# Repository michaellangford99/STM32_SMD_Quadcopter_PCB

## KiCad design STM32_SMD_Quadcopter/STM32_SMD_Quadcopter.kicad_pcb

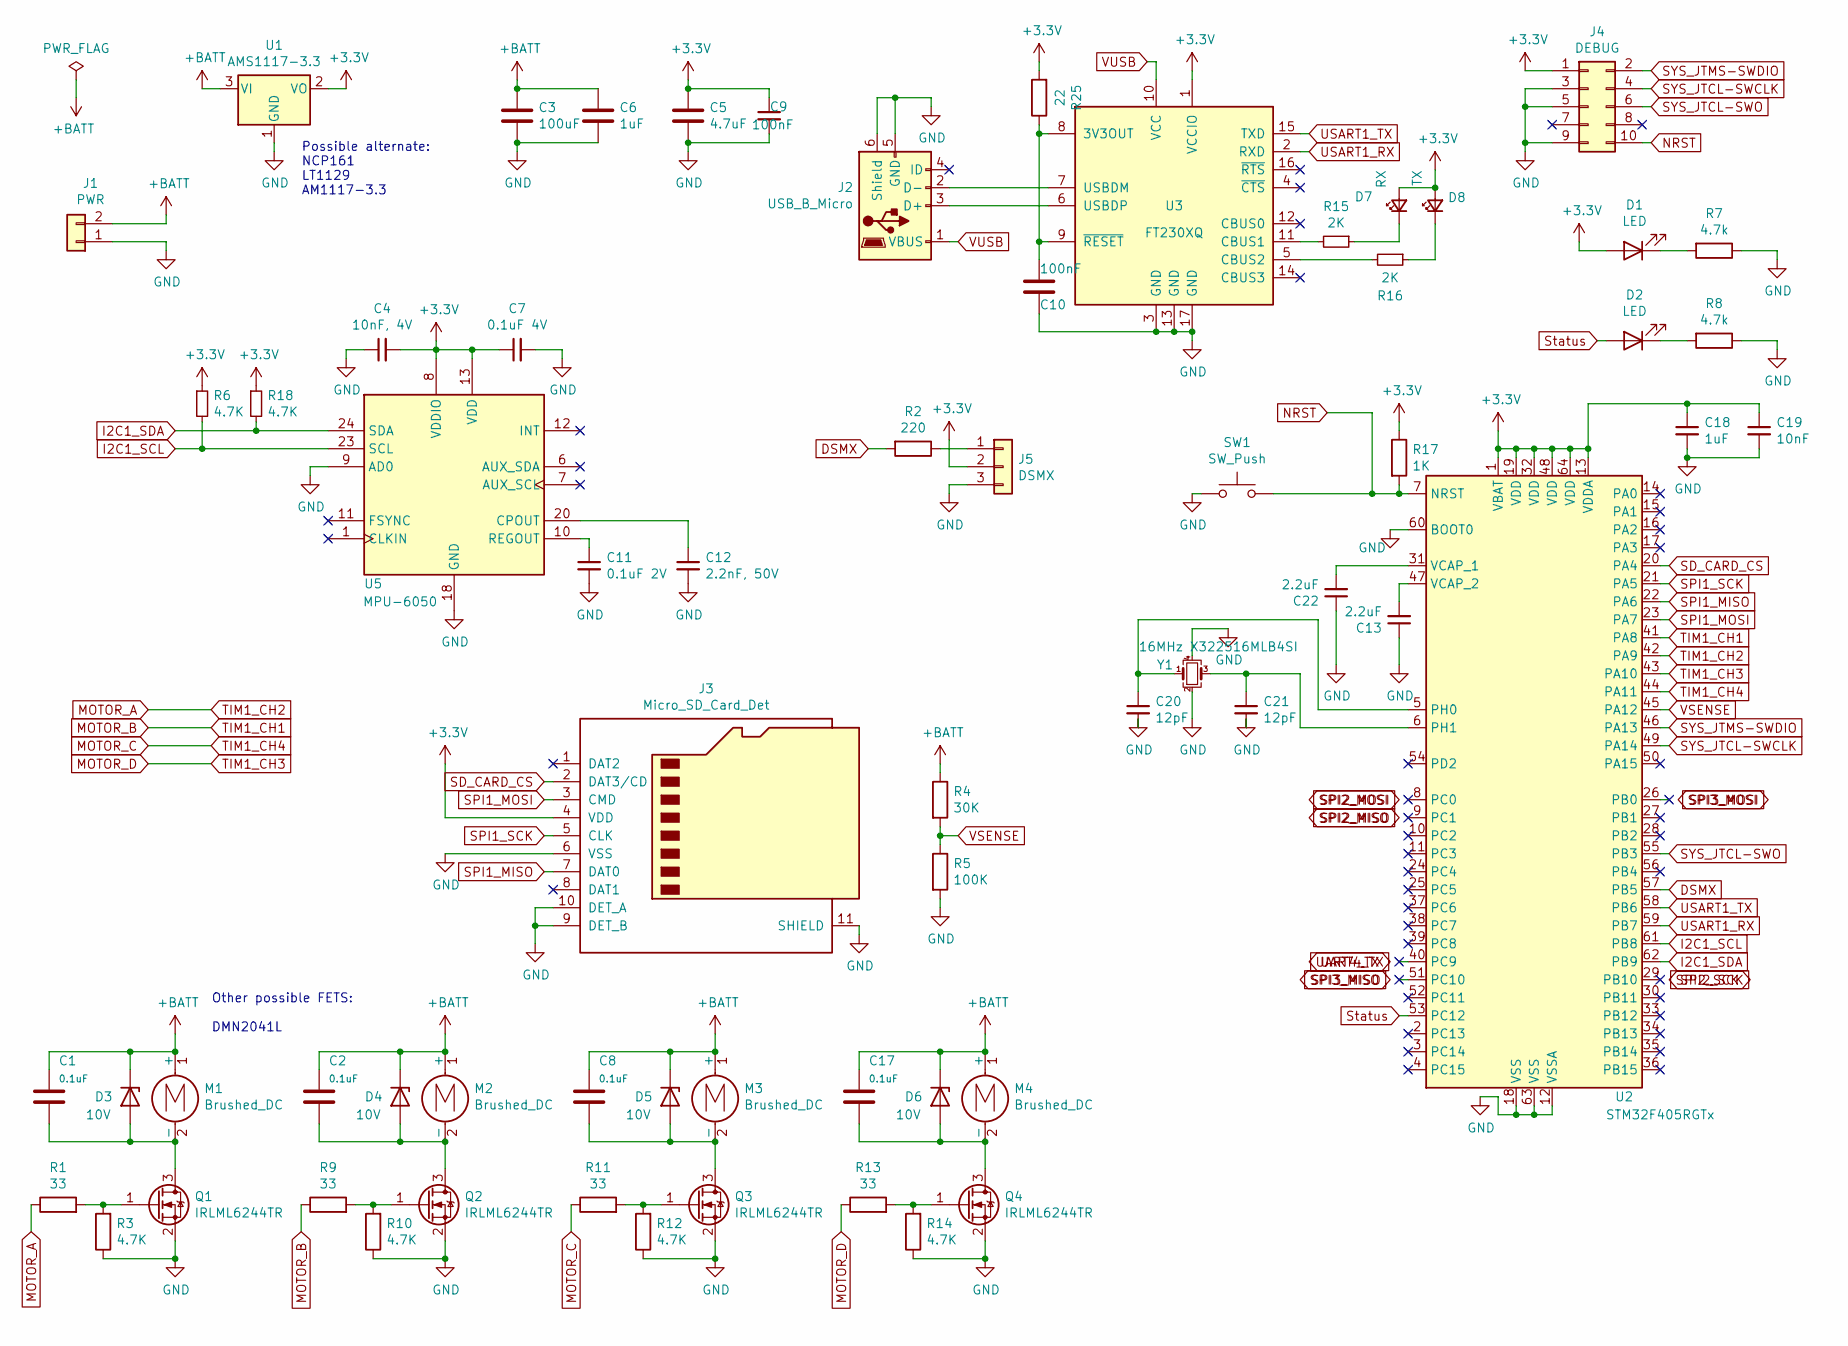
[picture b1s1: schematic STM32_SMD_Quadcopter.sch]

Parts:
C1, C2, C8, C17: 0.1uF; C_0402_1005Metric; LCSC Part # C1525
C3: 100uF; C_Elec_3x5.4; JLCPCB BOM 0
C4: 10nF, 4V; C_0402_1005Metric; LCSC Part # C15195
C5: 4.7uF; C_1210_3225Metric; JLCPCB BOM 0
C6, C18: 1uF; C_0603_1608Metric; LCSC Part # C15849
C7: 0.1uF 4V; C_0402_1005Metric; LCSC Part # C1525
C9, C10: 100nF; C_0402_1005Metric; LCSC Part # C1525
C11: 0.1uF 2V; C_0402_1005Metric; LCSC Part # C1525
C12: 2.2nF, 50V; C_0805_2012Metric; LCSC Part # C28260
C13, C22: 2.2uF; C_0603_1608Metric; LCSC Part # C23630
C19: 10nF; C_0603_1608Metric; LCSC Part # C57112
C20, C21: 12pF; C_0603_1608Metric; LCSC Part # C38523
D1: LED; LED_0603_1608Metric; LCSC Part # C72038
D2: LED; LED_0603_1608Metric; LCSC Part # C72043
D3, D4, D5, D6: 10V; D_0805_2012Metric; JLCPCB BOM 0
D7: RX; LED_0603_1608Metric; LCSC Part # C72041
D8: TX; LED_0603_1608Metric; LCSC Part # C2286
J1: PWR; PinHeader_1x02_P2.54mm_Vertical; JLCPCB BOM 0
J2: USB_B_Micro; USB_Micro-B_Molex_47346-0001; JLCPCB BOM 0
J3: Micro_SD_Card_Det; microSD_HC_Hirose_DM3D-SF; JLCPCB BOM 0
J4: DEBUG; PinSocket_2x05_P1.27mm_Vertical_SMD; JLCPCB BOM 0
J5: DSMX; PinHeader_1x03_P2.54mm_Vertical; JLCPCB BOM 0
M1, M2, M3, M4: Brushed_DC; PinHeader_1x02_P2.00mm_Vertical; JLCPCB BOM 0
Q1, Q2, Q3, Q4: IRLML6244TR; SOT-23_Handsoldering; JLCPCB BOM 0
R1, R9, R11, R13: 33; R_0603_1608Metric; LCSC Part # C23140
R2: 220; R_0603_1608Metric; LCSC Part # C22962
R3, R6, R10, R12, R14, R18: 4.7K; R_0603_1608Metric; LCSC Part # C23162
R4: 30K; R_0603_1608Metric; LCSC Part # C22984
R5: 100K; R_0603_1608Metric; LCSC Part # C25803
R7, R8: 4.7k; R_0603_1608Metric; LCSC Part # C23162
R15, R16: 2K; R_0603_1608Metric; LCSC Part # C22975
R17: 1K; R_0603_1608Metric; LCSC Part # C21190
R25: 22; R_0402_1005Metric; LCSC Part # C25092
SW1: SW_Push; SW_SPST_B3U-1000P; JLCPCB BOM 0
U1: AMS1117-3.3; SOT-223-3_TabPin2; JLCPCB BOM 0
U2: STM32F405RGTx; LQFP-64_10x10mm_P0.5mm
U3: FT230XQ; QFN-16-1EP_4x4mm_P0.65mm_EP2.5x2.5mm; LCSC Part # C128629
U5: MPU-6050; InvenSense_QFN-24_4x4mm_P0.5mm; LCSC Part # C24112
Y1: 16MHz X322516MLB4SI; Crystal_SMD_3225-4Pin_3.2x2.5mm; LCSC Part # C13738

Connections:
+3V3: C4.2, C5.1, C7.1, C9.1, C18.1, C19.1, D1.2 (A), D7.2 (A), D8.2 (A), J3.4 (VDD), J4.1, J5.2, R6.1, R17.1, R18.1, R25.2, U1.2 (VO), U2.1 (VBAT), U2.13 (VDDA), U2.19 (VDD), U2.32 (VDD), U2.48 (VDD), U2.64 (VDD), U3.1 (VCCIO), U5.8 (VDDIO), U5.13 (VDD); also elsewhere on the board
+BATT: C1.1, C2.1, C3.1, C6.1, C8.1, C17.1, D3.1 (K), D4.1 (K), D5.1 (K), D6.1 (K), J1.2, M1.1 (+), M2.1 (+), M3.1 (+), M4.1 (+), R4.1, U1.3 (VI)
DSMX: R2.2, U2.57 (PB5); also elsewhere on the board
I2C1_SCL: R6.2, U2.61 (PB8), U5.23 (SCL); also elsewhere on the board
I2C1_SDA: R18.2, U2.62 (PB9), U5.24 (SDA); also elsewhere on the board
MOTOR_A: R1.1, U2.42 (PA9); also elsewhere on the board
MOTOR_B: R9.1, U2.41 (PA8); also elsewhere on the board
MOTOR_C: R11.1, U2.44 (PA11); also elsewhere on the board
MOTOR_D: R13.1, U2.43 (PA10); also elsewhere on the board
NRST: J4.10, R17.2, SW1.2, U2.7 (NRST); also elsewhere on the board
unnamed: C1.2, D3.2 (A), M1.2 (-), Q1.3 (D)
unnamed: C2.2, D4.2 (A), M2.2 (-), Q2.3 (D)
unnamed: C8.2, D5.2 (A), M3.2 (-), Q3.3 (D)
unnamed: C10.2, R25.1, U3.8 (3V3OUT), U3.9 (~RESET)
unnamed: C11.1, U5.10 (REGOUT)
unnamed: C12.1, U5.20 (CPOUT)
unnamed: C13.2, U2.47 (VCAP_2)
unnamed: C17.2, D6.2 (A), M4.2 (-), Q4.3 (D)
unnamed 18: C20.1, U2.5 (PH0), Y1.1; also elsewhere on the board
unnamed 19: C21.1, U2.6 (PH1), Y1.3; also elsewhere on the board
unnamed: D1.1 (K), R7.2
unnamed: D2.1 (K), R8.2
unnamed: D7.1 (K), R15.1
unnamed: D8.1 (K), R16.1
unnamed: J2.2 (D-), U3.7 (USBDM)
unnamed: J2.3 (D+), U3.6 (USBDP)
unnamed: J5.1, R2.1
unnamed: Q1.1 (G), R1.2, R3.2
unnamed: Q2.1 (G), R9.2, R10.2
unnamed: Q3.1 (G), R11.2, R12.2
unnamed: Q4.1 (G), R13.2, R14.2
unnamed: R15.2, U3.11 (CBUS1)
unnamed: R16.2, U3.5 (CBUS2)
SD_CARD_CS: J3.2 (DAT3/CD), U2.20 (PA4); also elsewhere on the board
SPI1_MISO: J3.7 (DAT0), U2.22 (PA6); also elsewhere on the board
SPI1_MOSI: J3.3 (CMD), U2.23 (PA7); also elsewhere on the board
SPI1_SCK: J3.5 (CLK), U2.21 (PA5); also elsewhere on the board
SYS_JTCL-SWCLK: J4.4, U2.49 (PA14); also elsewhere on the board
SYS_JTCL-SWO: J4.6, U2.55 (PB3); also elsewhere on the board
SYS_JTMS-SWDIO: J4.2, U2.46 (PA13); also elsewhere on the board
Status: D2.2 (A), U2.53 (PC12); also elsewhere on the board
USART1_RX: U2.59 (PB7), U3.2 (RXD); also elsewhere on the board
USART1_TX: U2.58 (PB6), U3.15 (TXD); also elsewhere on the board
VSENSE: R4.2, R5.1, U2.45 (PA12); also elsewhere on the board
VUSB: J2.1 (VBUS), U3.10 (VCC)

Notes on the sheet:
Other possible FETS: DMN2041L
Possible alternate: NCP161 LT1129 AM1117-3.3

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
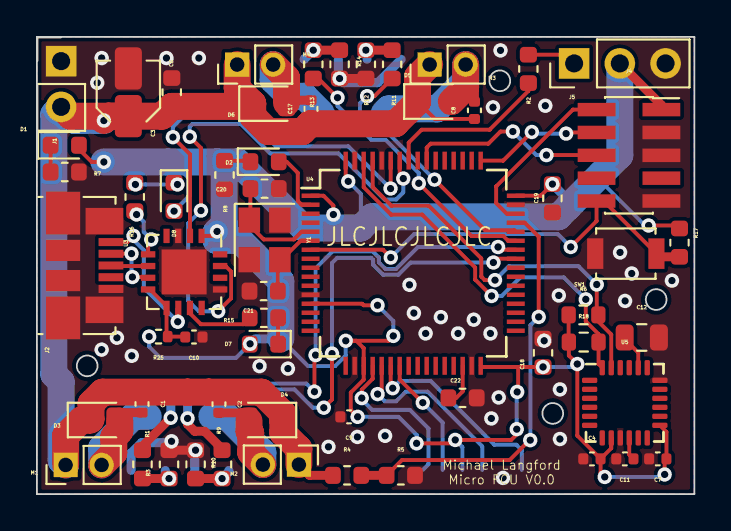
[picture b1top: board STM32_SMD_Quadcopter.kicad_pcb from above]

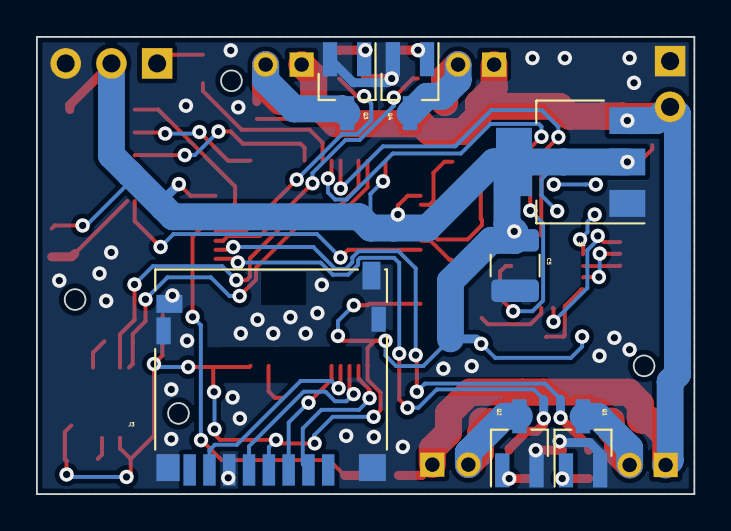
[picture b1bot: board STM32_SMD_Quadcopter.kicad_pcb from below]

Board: 2 copper layers, 36.5 x 25.4 mm, 64 parts (7 on the bottom side), 46 nets.

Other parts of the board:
U4: STM32F446RETx; LQFP-64_10x10mm_P0.5mm

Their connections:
+3V3: U4.1, U4.13, U4.19, U4.32, U4.48, U4.64; also elsewhere on the board
DSMX: U4.57; also elsewhere on the board
I2C1_SCL: U4.61; also elsewhere on the board
I2C1_SDA: U4.62; also elsewhere on the board
MOTOR_A: U4.42; also elsewhere on the board
MOTOR_B: U4.41; also elsewhere on the board
MOTOR_C: U4.44; also elsewhere on the board
MOTOR_D: U4.43; also elsewhere on the board
NRST: U4.7; also elsewhere on the board
unnamed 18: U4.5; also elsewhere on the board
unnamed 19: U4.6; also elsewhere on the board
SD_CARD_CS: U4.20; also elsewhere on the board
SPI1_MISO: U4.22; also elsewhere on the board
SPI1_MOSI: U4.23; also elsewhere on the board
SPI1_SCK: U4.21; also elsewhere on the board
SYS_JTCL-SWCLK: U4.49; also elsewhere on the board
SYS_JTCL-SWO: U4.55; also elsewhere on the board
SYS_JTMS-SWDIO: U4.46; also elsewhere on the board
Status: U4.2; also elsewhere on the board
USART1_RX: U4.59; also elsewhere on the board
USART1_TX: U4.58; also elsewhere on the board
VSENSE: U4.45; also elsewhere on the board

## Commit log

2020-04-13 regulator, power over USB, compact SMD, 0603 min cap size
2020-04-14 Latest model, no traces, old crystal
2020-04-16 Made much denser, added traces
2020-04-16 Completed board v1
2020-04-16 Completed board v1 and added files
2020-04-17 fixed silkscreen
2020-04-20 Finished gerbers
2020-11-25 Latest update
2020-11-27 V2 started, using different crystal, ICM20948, 10 pin SWD header, and multiple component swaps
2020-11-27 All parts set in place
2020-11-28 completed switchover to MPU6050
2020-11-28 Finished and almost ready for purchase, with stm32f446RET6 and FT230XQ
2021-03-11 Purchase version
